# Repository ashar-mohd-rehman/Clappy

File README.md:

# Clappy
Seeed Studio XIAO RP2040 based custom 8-key mechanical macropad called clappy. It features a 8 switch diode matrix, EC11 rotary encoder for volume knob and a 128x64 I2C OLED display for layer and volume percentage visuals. Designed in KiCad and uses KMK firmware.

**WHY I MADE THIS?** I really like minecraft pvp, But switching to hotbar with scroll wheel is not very precise and loses time, The time lost is an advantage to your opponent, You can use the number row on your keyboard, But that is very hard for me to reach, while moving with WASD especially with very short hands

So I decided to make this macropad which will help me in minecraft pvp and moreover I am a massive cad user, using macropad to pan, tilt, rotate instead of shortcuts will help me save time

# Schematic

# PCB

# Case 

# BOM
https://docs.google.com/spreadsheets/d/1dtDxAbcGN6YtRzD2a8uUHmDw_Tfo3L7_lsSwaDiVz0I/edit?usp=sharing

| Part Name | Quantity | Unit Cost ($) | Link |
| :--- | :---: | :---: | :--- |
| **Diodes SOD-123** | 8 | $0.96 | [Robu.in Link](https://robu.in/product/1n4148w-sod-123-1206-diodereel-of-3000/) |
| **OLED 1.3 inch** | 1 | $3.78 | [Robu.in Link](https://robu.in/product/1-3-inch-i2c-iic-oled-lcd-module-4pin-with-vcc-gnd-white/) |
| **Switches** | 10 | $3.95 | [Meckeys Link](https://meckeys.com/shop/accessories/keyboard-accessories/key-switches/cherry-mx-rgb-switch/) |
| **EC11 Rotary Encoder** | 1 | $0.0061 | [Robu.in Link](https://robu.in/product/hongyan-ec11h-7ce15p1zy15f7-rotary-encoder-with-push-button-switch-vertical-plug-in/) |
| **XIAO-RP2040** | 1 | $5.57 | [Robu.in Link](https://robu.in/product/seeed-studio-xiao-rp2040-v1-0/) |
| **Kailh Hot-swap Socket** | 10 | $0.80 | [Meckeys Link](https://meckeys.com/shop/accessories/keyboard-accessories/key-switches/kailh-hot-swap-socket/) |
| **PCB** | 5 | $2.00 | [JLCPCB Quote](https://cart.jlcpcb.com/quote) |
| **Shipping** | 1 | $9.83 | — |
| **Total** | — | **$26.90** | — |

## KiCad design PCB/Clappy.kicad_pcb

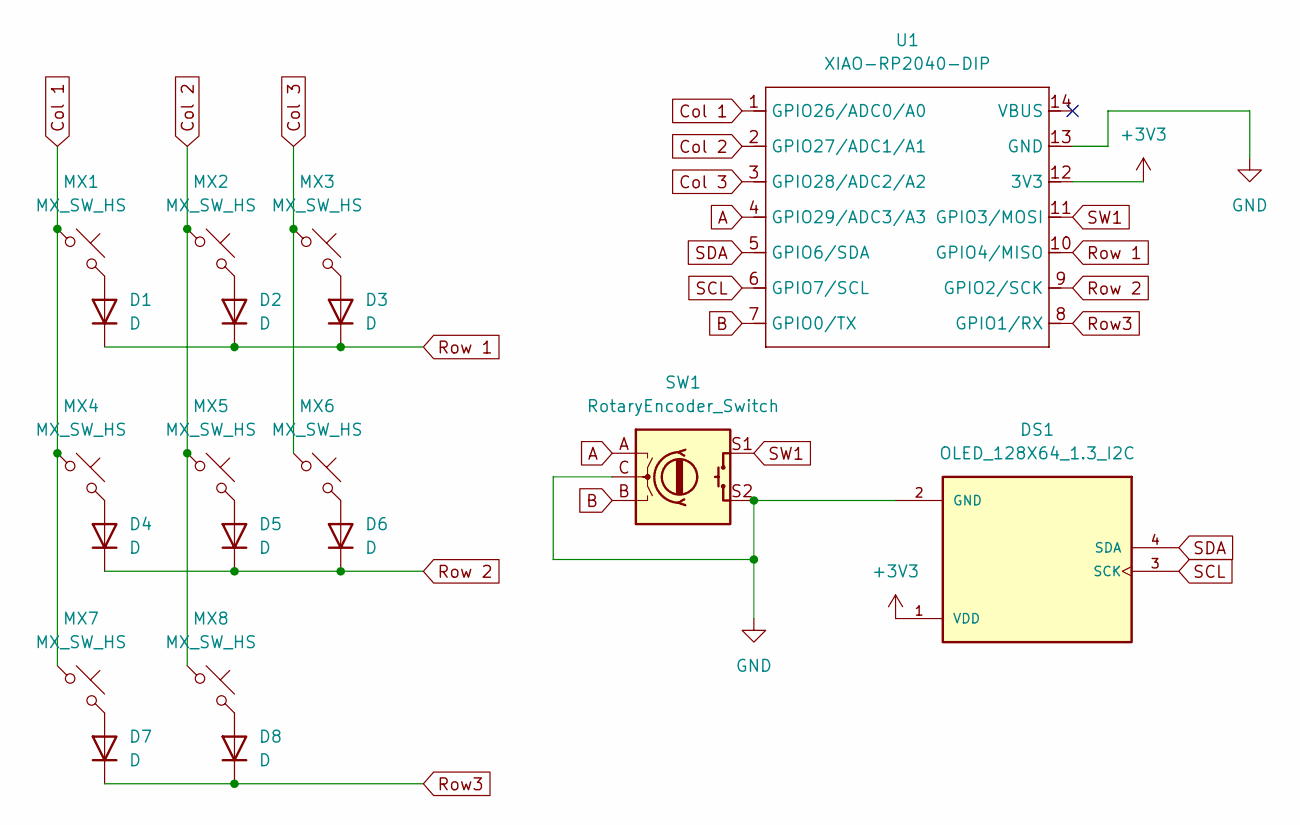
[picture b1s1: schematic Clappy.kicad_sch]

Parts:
D1, D2, D3, D4, D5, D6, D7, D8: D; D_SOD-123
DS1: OLED_128X64_1.3_I2C; LCD_OLED_128X64_1.3_I2C; PARTREV NA
MX1, MX2, MX3, MX4, MX5, MX6, MX7, MX8: MX_SW_HS; SW_MX_HS_CPG151101S11_1u
SW1: RotaryEncoder_Switch; RotaryEncoder_Alps_EC11E-Switch_Vertical_H20mm
U1: XIAO-RP2040-DIP

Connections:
+3V3: DS1.1 (VDD), U1.12 (3V3)
A: SW1.A, U1.4 (GPIO29/ADC3/A3)
B: SW1.B, U1.7 (GPIO0/TX)
Col 1: MX1.1, MX4.1, MX7.1, U1.1 (GPIO26/ADC0/A0)
Col 2: MX2.1, MX5.1, MX8.1, U1.2 (GPIO27/ADC1/A1)
Col 3: MX3.1, MX6.1, U1.3 (GPIO28/ADC2/A2)
GND: DS1.2 (GND), SW1.C, SW1.S2, U1.13 (GND)
unnamed: D1.2 (A), MX1.2
unnamed: D2.2 (A), MX2.2
unnamed: D3.2 (A), MX3.2
unnamed: D4.2 (A), MX4.2
unnamed: D5.2 (A), MX5.2
unnamed: D6.2 (A), MX6.2
unnamed: D7.2 (A), MX7.2
unnamed: D8.2 (A), MX8.2
Row3: D7.1 (K), D8.1 (K), U1.8 (GPIO1/RX)
Row 1: D1.1 (K), D2.1 (K), D3.1 (K), U1.10 (GPIO4/MISO)
Row 2: D4.1 (K), D5.1 (K), D6.1 (K), U1.9 (GPIO2/SCK)
SCL: DS1.3 (SCK), U1.6 (GPIO7/SCL)
SDA: DS1.4 (SDA), U1.5 (GPIO6/SDA)
SW1: SW1.S1, U1.11 (GPIO3/MOSI)

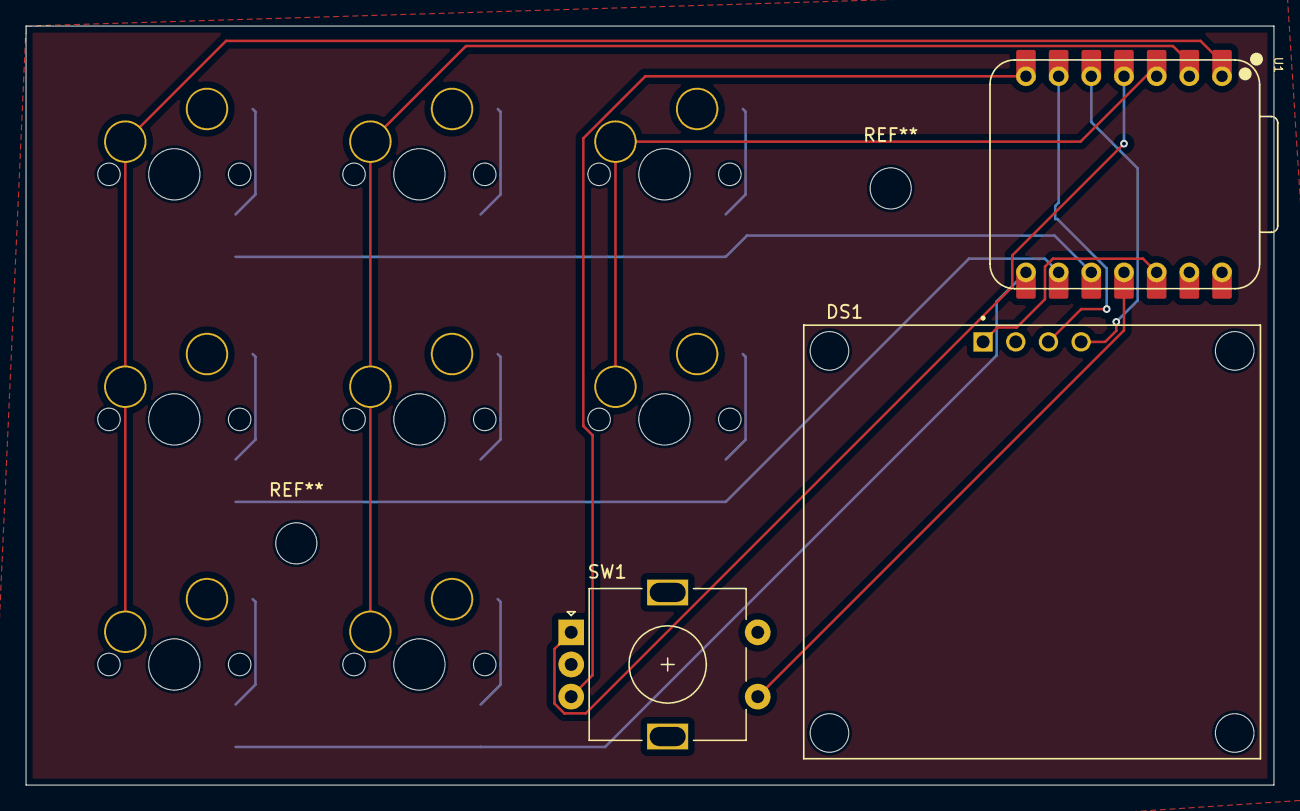
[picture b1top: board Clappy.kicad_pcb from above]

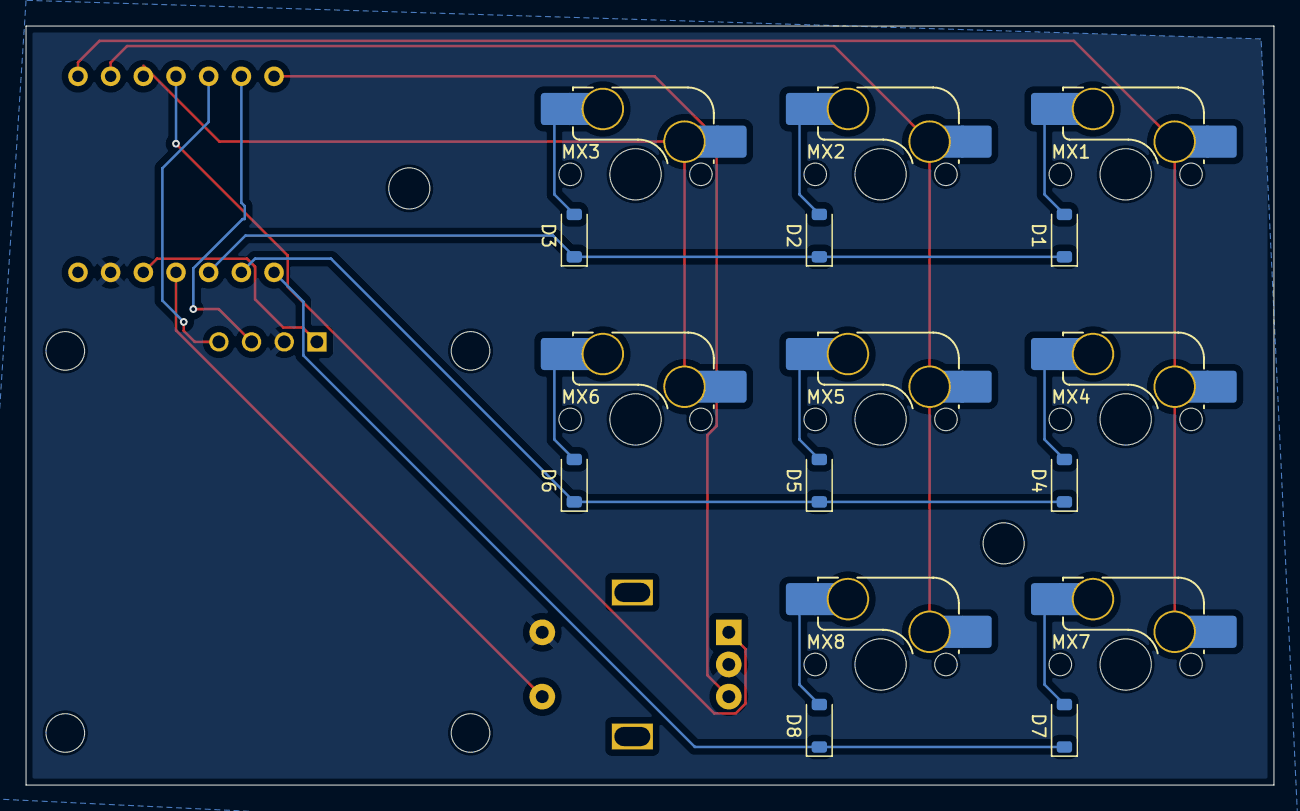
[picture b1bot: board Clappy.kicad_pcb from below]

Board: 2 copper layers, 97.0 x 59.0 mm, 19 parts (16 on the bottom side), 21 nets.
